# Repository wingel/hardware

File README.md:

# Miscellaneous hardware projects by Christer Weinigel

See [LICENSE.md](LICENSE.md) for licensing.

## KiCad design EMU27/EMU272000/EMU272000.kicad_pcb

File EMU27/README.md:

# En 27 series EPROM emulator

An 27-series EPROM emulator with in circuit programming.

This is the first spin and the hardware won't work properly.  /CS is
ignored so unless the EEPROM is the only device on the memory bus
reads from it can conflict with reads from other devices.

Planned EPROM variants:

| Model       | Package | Size (bits) | Size (words) | Comments		|
| ----------- | ------: | ----------: | -----------: | ----------------	|
| 27C1000     |   DIP32 |          1M |     128k x 8 |                  |
| 27C2000     |   DIP32 |          2M |     256k x 8 |                  |

# Description

A 3.3V flash memory with is used to store data.  A 5V tolerant CPLD
and a level shifter is used to do level translation between the 3.3V
flash memory and the 5V EEPROM pins.  The CPLD and level shifter can
also isolate the flash memory from the EEPROM pins so that the flash
memory can be progammed in circuit.  The 3.3V supply for the CPLD and
flash memory can be supplied from either the EEPROM pins or from the
programming connector so that the flash can be reprogrammed when the
cirucit is turned off.

The flash memory can be programmed using JTAG boundary scan using the
same JTAG connector which is also used to program the CPLD or using
(TBD - protocol to be decided) over a separate in circuit programming
connector.

PDF files with the schematics can be found in the [Docs](Docs)
directory.

# Operation

The emulator consists of two bords.  The main board (27C2000C)
contains the CPLD, flash memory and programming connectors.  Another
board contains (27C2000) the level shifter, 5V to 3.3V power supply
and EPROM pins that fit a EPROM socket.  The main reason for using two
boards are size constraints, it's hard to find a CPLD with enough pins
which can be hand soldered and which will fit between the DIP pins.
The current variant of the second board has a DIP32 footprint and
should be compatible with 27C1000 and 27C2000 EPROMs, but it should be
easy to adapt this design to to other pinouts and smaller EPROMS.

The CPLD is connected to the address (A0_5V..A17_5V) and control
(CE_5V and OE_5V) pins on the 5V EPROM side and the address (A0..A17),
data (D0..D7) and control (CE, OE and WE) on the 3.3V flash memory
side.  A level shifter also interfaces between the 5V data
(D0_5V..D7_5V) and 3.3V data (D0..D7) pins.  In normal operation the
CPLD drives the 3.3V A0..A7, CE and OE pins with the signals from the
corresponding signals on the 5V side.  The level shifter drives the 5V
D0_5V..D7_5V pins the 3.3V data pins whenever OE_5V and CE_5V are low.

TODO this is not true right now, the circuit is buggy and will drive
the D0_5V..D7_5V pins whenever OE is low; the state of CE is ignored.
This has to be fixed in a future spin of the emulator.

The reason for using a separate level shifter is mostly that I could
not find a CPLD that can be hand soldered and which would have enough
pins and fit physically on the board.  A bonus though of using a
separate level shifter is that it will actually drive 5V onto the
D0_5V..D7_5V pins which could improve compatibility if the emulator is
used in a circuit which won't work if they were driven with 3.3V.

# Tools

The [tools](tools) directory contains some quick python hacks to talk
to the emulator using JTAG boundary scan using openocd.  This
directory also contains an openocd configuration for a Raspberry Pi 3.

[emu2000_bsdl.py](tools/emu2000_bsdl.py) uses boundary scan to show
the state all pins on the emulator and toggles one of the programming
lines just to see that it can be done.

[emu2000_prog.py](tools/emu2000_prog.py) uses boundary scan to program
the first 256 bytes of the flash memory with some test data.

If you have a minipro compatible PROM programmer you can plug the
emulator into it and read out the test data with:

```bash
sudo ./minipro -p 'MX27C1000@DIP32' -r foo.bin -y
```

The "-y" flag is neccessary because the emulator is actually more of a
ROM emulator and does not present the correct chip ID:

```
Found TL866II+ 04.2.86 (0x256)
Warning: Firmware is out of date.
  Expected  04.2.128 (0x280)
    Found     04.2.86 (0x256)
    WARNING: Chip ID mismatch: expected 0xC20E, got 0xFFFF (unknown)
    Reading Code...  1.05Sec  OK
```

You will need a BSDL file for the Xilinx XC9572XL chip.  The tools
assume that Xilinx ISE is installed /opt/Xilinx and that the BSDL file
is called /opt/Xilinx/14.7/ISE_DS/ISE/xc9500xl/data/xc9572xl_vq64.bsd .

To be abls to read BSDL files this BSDL parser is used:

> https://github.com/cyrozap/python-bsdl-parser

The minipro tool can be found here:

> https://gitlab.com/DavidGriffith/minipro

# Bugs and possible improvements

CE is ignored when deciding to drive D0_5V..D7_5V, only OE is
considered.  This means that if CE is actually used as a chip select,
reads from the emulator will conflict with reads from other devices.
This can be worked around by removing R2 or U3 and driving the DIR pin
of U2 from CE (TODO have to check the polarity).  In the future,
figure out a better way of doing this.  Decode CE and OE using the
CPLD and use a free pin to drive OE of U3.  Or do it with discrete
logic (CE_5V connected to OE of U3, OE_5V connected to DIR or the
inverter).

The current spin of the emulator was intended to have an onboard
oscillator and have two two programming signals using I2C or UART.
I'm probably going to switch to using a bidirectional variant of SPI
where the SCK signal replaces the oscillator.  One less component to
mount on the PCB and this ought to simplify the logic in the FPGA
quite a bit.

Currently A18 is connected to the flash memory so that a 512kx8 flash
could be used.  That's a bit unneccesary, drive A18 low or leave it
floating instead and just don't support a larger flash than 256kx8.
This would also free up a pin on the CPLD.

It might be possible to pull CE on the flash chip to ground
permanently so that it does not have to be connected to the CPLD.
If that can be done that would free up one pin on the CPLD.

Currently A17_5V and PGM_5V are not connected to the CPLD.  Those pins
are used for the programming interface.  Relocate A17 to some other
CPLD pin so that 27C2000 emulation will work.

It would be nice if the emulation could emulate not only a ROM but
acually a PROM which responds with an ID code.  To do that we'd need
to be able to observe the PGM pin and see if it is pulled to +12V.
Not that important, but would be nice to have.

Rename the mainboard to 27EMUMAIN or maybe EMU27MAIN.

Maybe rename the other board to EMU271000.

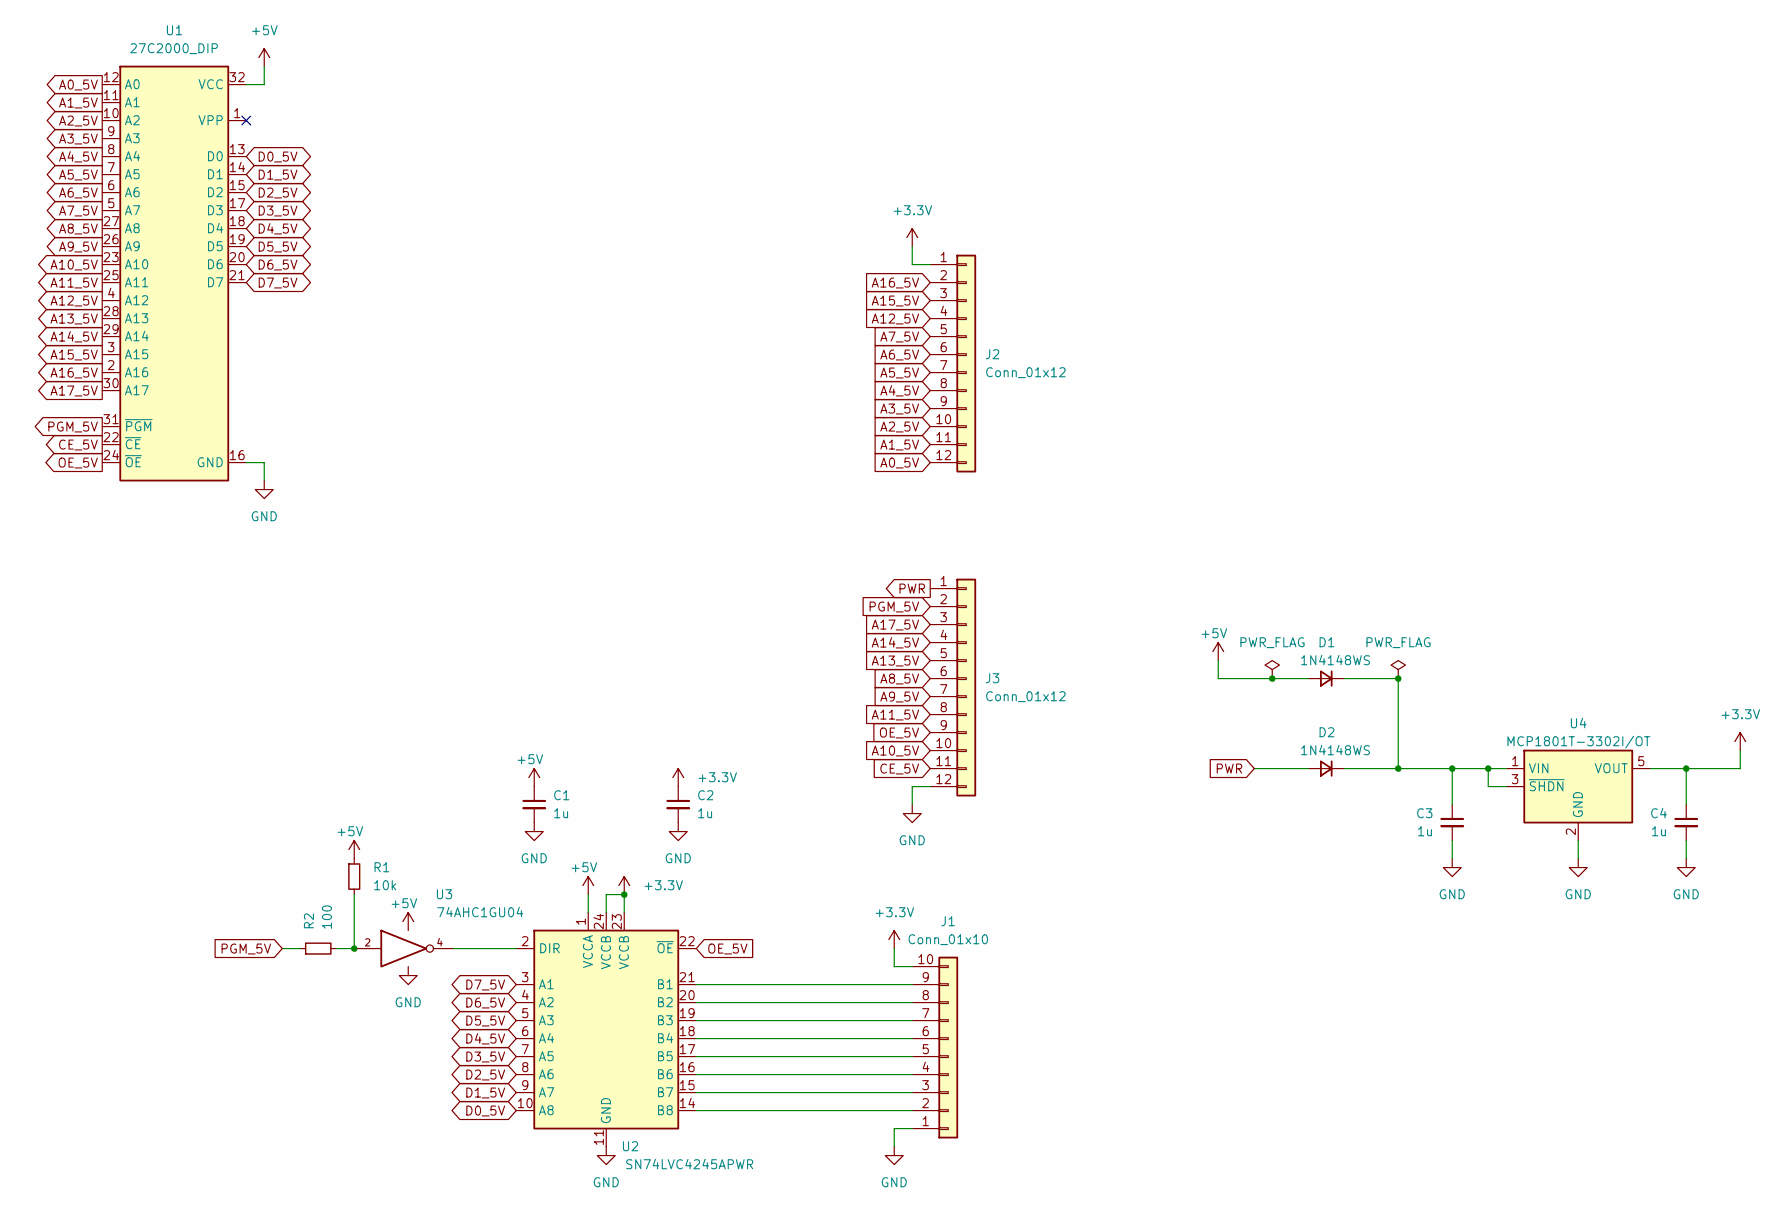
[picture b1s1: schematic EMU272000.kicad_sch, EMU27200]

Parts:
C1, C2, C3, C4: 1u; R_0603_1608Metric_Pad0.98x0.95mm_HandSolder; LCSC C52923
D1, D2: 1N4148WS; D_SOD-323F; LCSC C2128
J1: Conn_01x10; PinHeader_1x10_P1.27mm_Vertical
J2, J3: Conn_01x12; PinHeader_1x12_P1.27mm_Vertical
R1: 10k; R_0603_1608Metric_Pad0.98x0.95mm_HandSolder; LCSC C25744
R2: 100; R_0603_1608Metric_Pad0.98x0.95mm_HandSolder; LCSC C25076
U1: 27C2000_DIP; DIP-32_W15.24mm_Socket
U2: SN74LVC4245APWR; TSSOP-24_4.4x7.8mm_P0.65mm; LCSC C7859
U3: 74AHC1GU04; SOT-23-5_HandSoldering; LCSC C7465
U4: MCP1801T-3302I/OT; SOT-23-5; LCSC C84119

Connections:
+3V3: C2.1, C4.1, J1.10, J2.1, U2.23 (VCCB), U2.24 (VCCB), U4.5 (VOUT)
+5V: C1.1, D1.2 (A), R1.1, U1.32 (VCC), U2.1 (VCCA), U3.5 (VCC)
A0_5V: J2.12, U1.12 (A0)
A1_5V: J2.11, U1.11 (A1)
A2_5V: J2.10, U1.10 (A2)
A3_5V: J2.9, U1.9 (A3)
A4_5V: J2.8, U1.8 (A4)
A5_5V: J2.7, U1.7 (A5)
A6_5V: J2.6, U1.6 (A6)
A7_5V: J2.5, U1.5 (A7)
A8_5V: J3.6, U1.27 (A8)
A9_5V: J3.7, U1.26 (A9)
A10_5V: J3.10, U1.23 (A10)
A11_5V: J3.8, U1.25 (A11)
A12_5V: J2.4, U1.4 (A12)
A13_5V: J3.5, U1.28 (A13)
A14_5V: J3.4, U1.29 (A14)
A15_5V: J2.3, U1.3 (A15)
A16_5V: J2.2, U1.2 (A16)
A17_5V: J3.3, U1.30 (A17)
CE_5V: J3.11, U1.22 (~CE)
D0_5V: U1.13 (D0), U2.10 (A8)
D1_5V: U1.14 (D1), U2.9 (A7)
D2_5V: U1.15 (D2), U2.8 (A6)
D3_5V: U1.17 (D3), U2.7 (A5)
D4_5V: U1.18 (D4), U2.6 (A4)
D5_5V: U1.19 (D5), U2.5 (A3)
D6_5V: U1.20 (D6), U2.4 (A2)
D7_5V: U1.21 (D7), U2.3 (A1)
GND: C1.2, C2.2, C3.2, C4.2, J1.1, J3.12, U1.16 (GND), U2.11 (GND), U2.12 (GND), U2.13 (GND), U3.3 (GND), U4.2 (GND)
unnamed: C3.1, D1.1 (K), D2.1 (K), U4.1 (VIN), U4.3 (~SHDN)
unnamed: J1.2, U2.14 (B8)
unnamed: J1.3, U2.15 (B7)
unnamed: J1.4, U2.16 (B6)
unnamed: J1.5, U2.17 (B5)
unnamed: J1.6, U2.18 (B4)
unnamed: J1.7, U2.19 (B3)
unnamed: J1.8, U2.20 (B2)
unnamed: J1.9, U2.21 (B1)
unnamed: R1.2, R2.2, U3.2
unnamed: U2.2 (DIR), U3.4
OE_5V: J3.9, U1.24 (~OE), U2.22 (~OE)
PGM_5V: J3.2, R2.1, U1.31 (~PGM)
PWR: D2.2 (A), J3.1

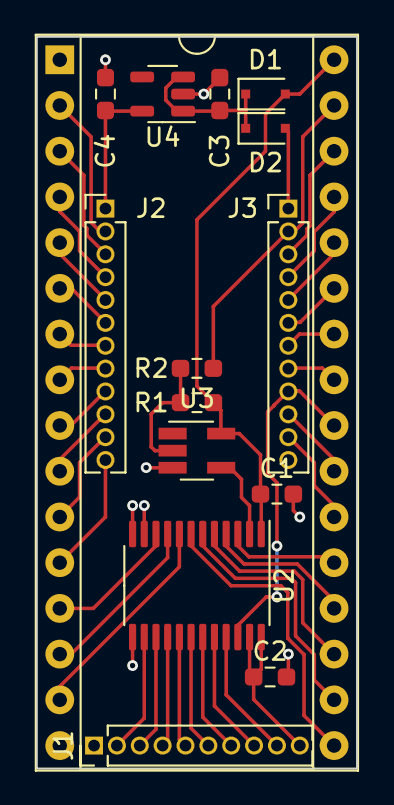
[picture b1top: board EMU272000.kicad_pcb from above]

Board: 2 copper layers, 17.8 x 40.6 mm, 15 parts (0 on the bottom side), 44 nets.

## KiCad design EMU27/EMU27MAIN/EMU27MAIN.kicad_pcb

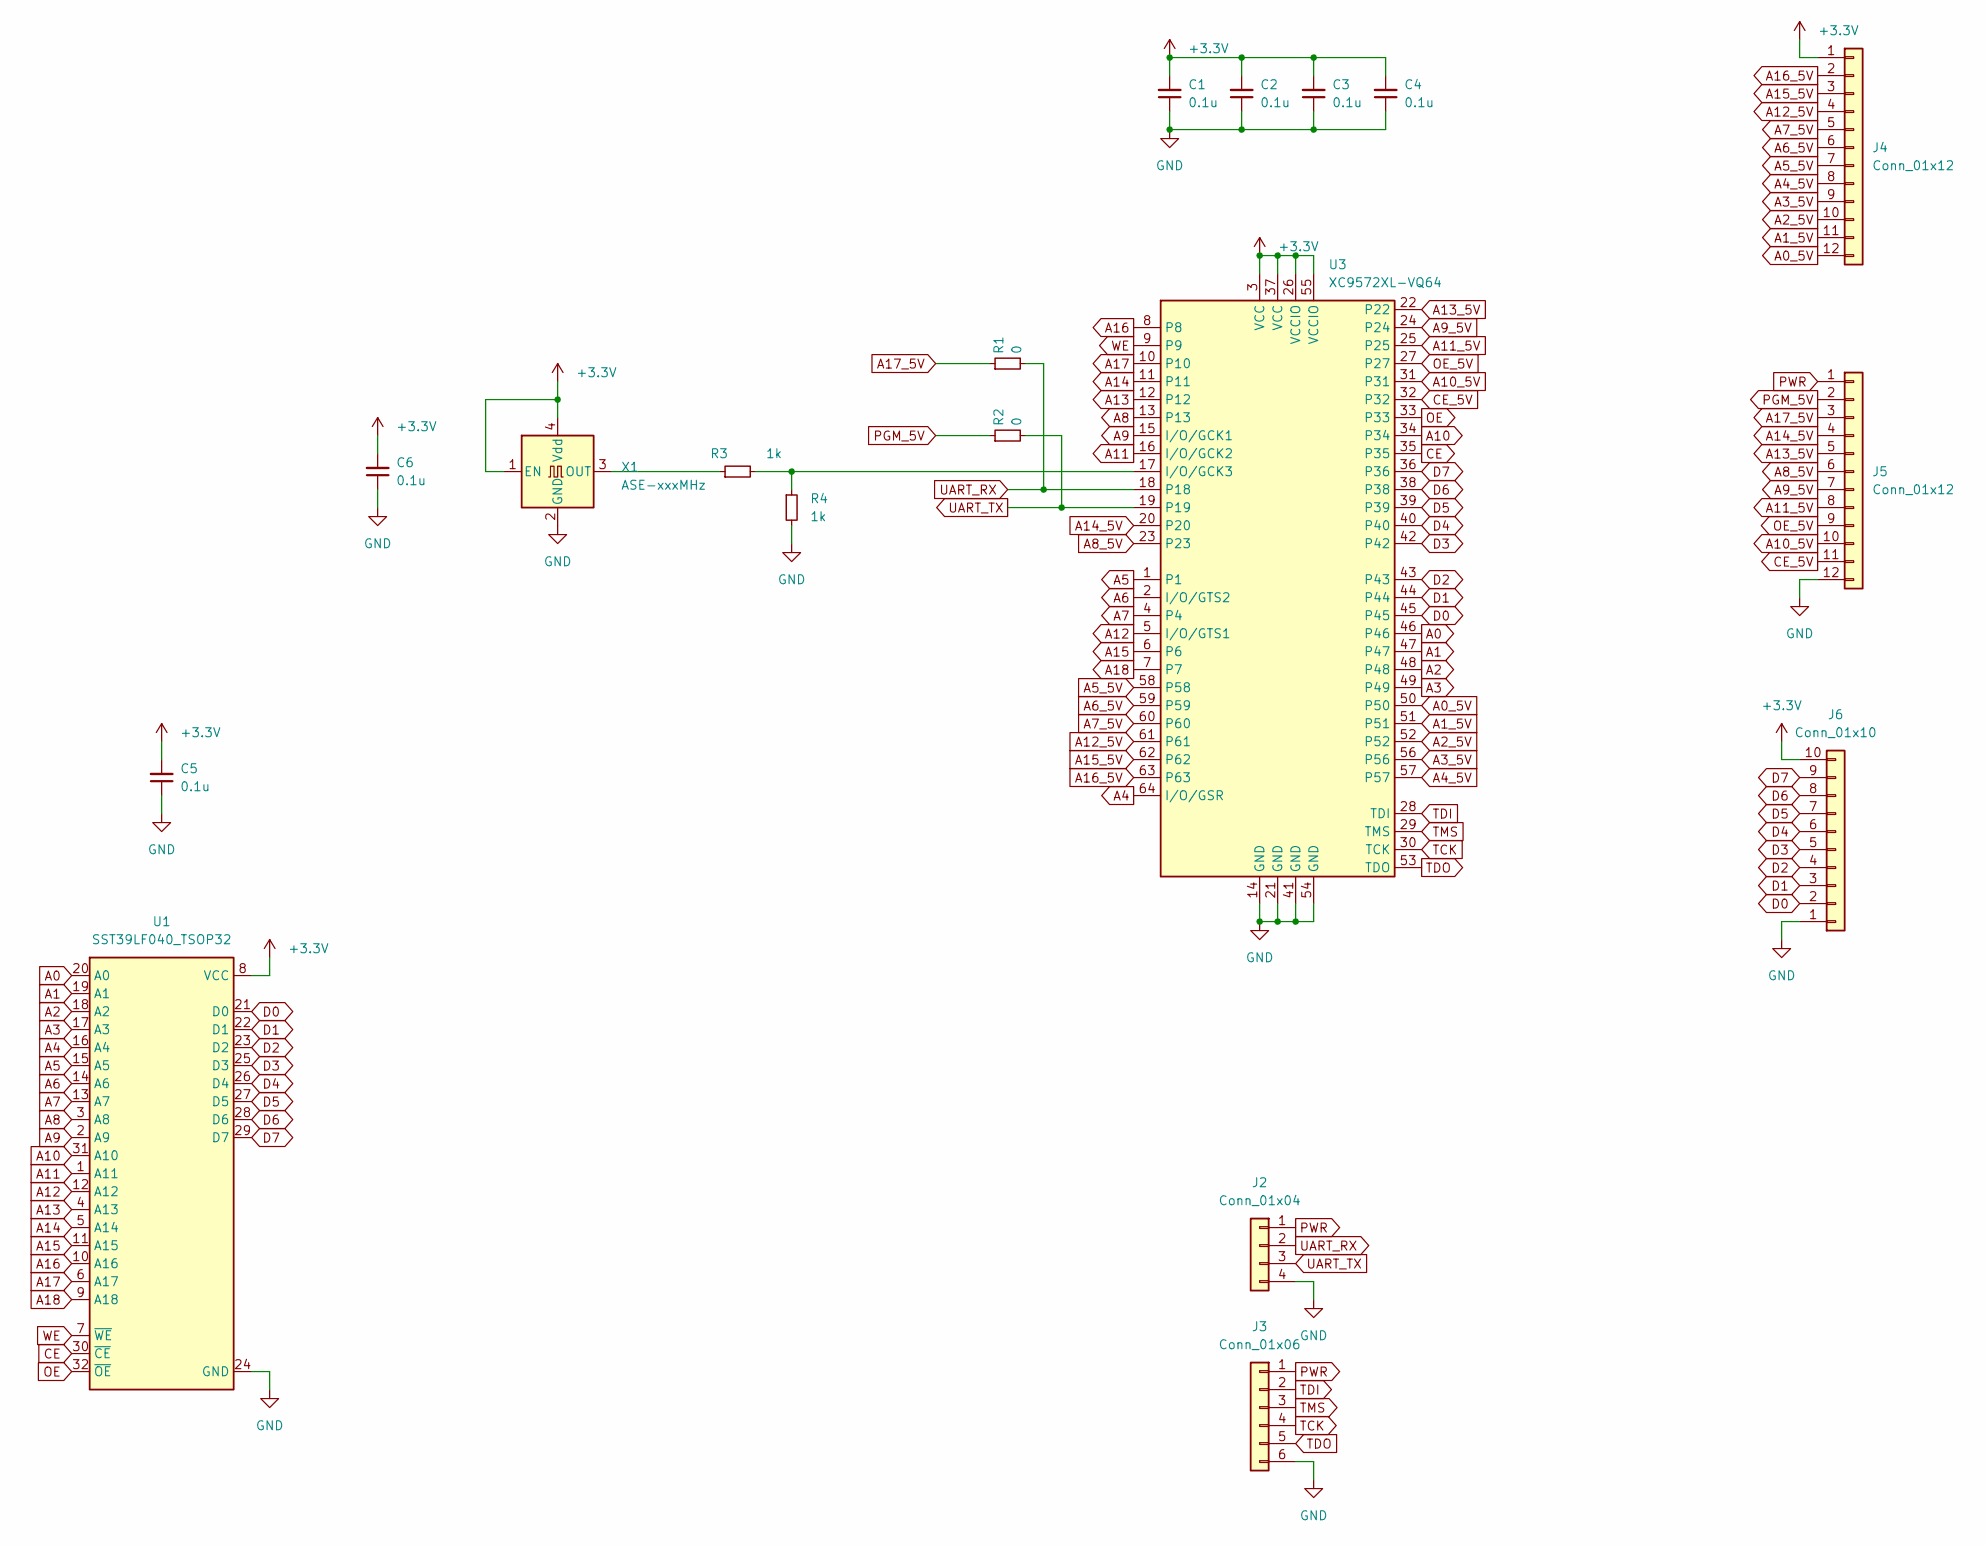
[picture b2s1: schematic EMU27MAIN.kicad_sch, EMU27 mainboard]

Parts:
C1, C2, C3, C4, C5, C6: 0.1u; R_0402_1005Metric; Voltage 16V; LCSC C1525
J2: Conn_01x04; Molex_PicoBlade_53047-0410_1x04_P1.25mm_Vertical
J3: Conn_01x06; Molex_PicoBlade_53047-0610_1x06_P1.25mm_Vertical
J4, J5: Conn_01x12; PinSocket_1x12_P1.27mm_Vertical
J6: Conn_01x10; PinSocket_1x10_P1.27mm_Vertical
R1, R2: 0; R_0402_1005Metric; LCSC C17168
R3, R4: 1k; R_0402_1005Metric
U1: SST39LF040_TSOP32; TSOP-I-32_12.4x8mm_P0.5mm
U3: XC9572XL-VQ64; TQFP-64_10x10mm_P0.5mm
X1: ASE-xxxMHz; Oscillator_SMD_Abracon_ASCO-4Pin_1.6x1.2mm

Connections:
+3V3: C1.2, C2.2, C3.2, C4.2, C5.2, C6.2, J4.1, J6.10, U1.8 (VCC), U3.3 (VCC), U3.26 (VCCIO), U3.37 (VCC), U3.55 (VCCIO), X1.1 (EN), X1.4 (Vdd)
A0: U1.20 (A0), U3.46
A0_5V: J4.12, U3.50
A1: U1.19 (A1), U3.47
A1_5V: J4.11, U3.51
A2: U1.18 (A2), U3.48
A2_5V: J4.10, U3.52
A3: U1.17 (A3), U3.49
A3_5V: J4.9, U3.56
A4: U1.16 (A4), U3.64 (I/O/GSR)
A4_5V: J4.8, U3.57
A5: U1.15 (A5), U3.1
A5_5V: J4.7, U3.58
A6: U1.14 (A6), U3.2 (I/O/GTS2)
A6_5V: J4.6, U3.59
A7: U1.13 (A7), U3.4
A7_5V: J4.5, U3.60
A8: U1.3 (A8), U3.13
A8_5V: J5.6, U3.23
A9: U1.2 (A9), U3.15 (I/O/GCK1)
A9_5V: J5.7, U3.24
A10: U1.31 (A10), U3.34
A10_5V: J5.10, U3.31
A11: U1.1 (A11), U3.16 (I/O/GCK2)
A11_5V: J5.8, U3.25
A12: U1.12 (A12), U3.5 (I/O/GTS1)
A12_5V: J4.4, U3.61
A13: U1.4 (A13), U3.12
A13_5V: J5.5, U3.22
A14: U1.5 (A14), U3.11
A14_5V: J5.4, U3.20
A15: U1.11 (A15), U3.6
A15_5V: J4.3, U3.62
A16: U1.10 (A16), U3.8
A16_5V: J4.2, U3.63
A17: U1.6 (A17), U3.10
A17_5V: J5.3, R1.1
A18: U1.9 (A18), U3.7
CE: U1.30 (~CE), U3.35
CE_5V: J5.11, U3.32
D0: J6.2, U1.21 (D0), U3.45
D1: J6.3, U1.22 (D1), U3.44
D2: J6.4, U1.23 (D2), U3.43
D3: J6.5, U1.25 (D3), U3.42
D4: J6.6, U1.26 (D4), U3.40
D5: J6.7, U1.27 (D5), U3.39
D6: J6.8, U1.28 (D6), U3.38
D7: J6.9, U1.29 (D7), U3.36
GND: C1.1, C2.1, C3.1, C4.1, C5.1, C6.1, J2.4, J3.6, J5.12, J6.1, R4.2, U1.24 (GND), U3.14 (GND), U3.21 (GND), U3.41 (GND), U3.54 (GND), X1.2 (GND)
unnamed: R3.1, X1.3 (OUT)
unnamed: R3.2, R4.1, U3.17 (I/O/GCK3)
OE: U1.32 (~OE), U3.33
OE_5V: J5.9, U3.27
PGM_5V: J5.2, R2.1
PWR: J2.1, J3.1, J5.1
TCK: J3.4, U3.30 (TCK)
TDI: J3.2, U3.28 (TDI)
TDO: J3.5, U3.53 (TDO)
TMS: J3.3, U3.29 (TMS)
UART_RX: J2.2, R1.2, U3.18
UART_TX: J2.3, R2.2, U3.19
WE: U1.7 (~WE), U3.9

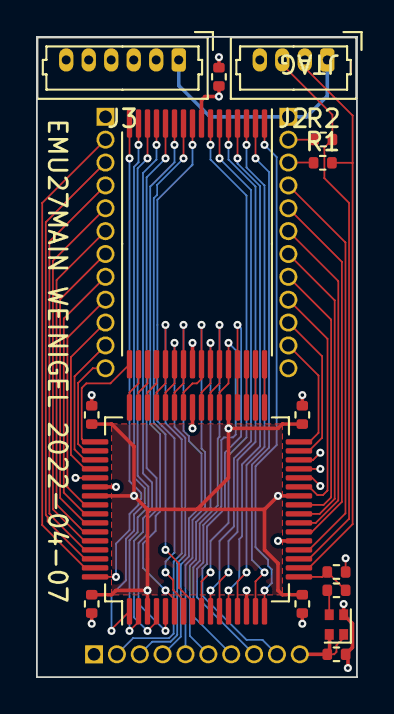
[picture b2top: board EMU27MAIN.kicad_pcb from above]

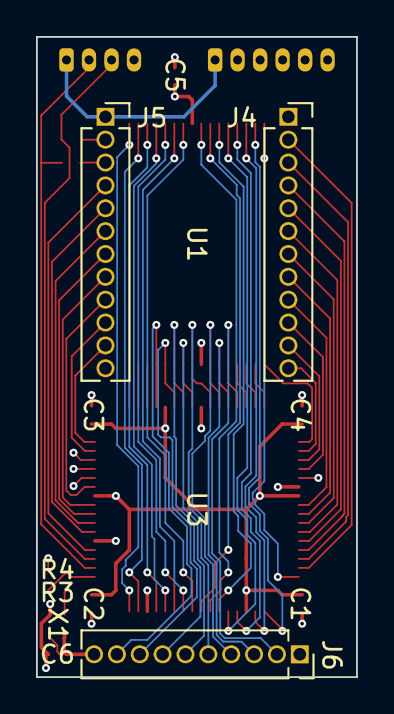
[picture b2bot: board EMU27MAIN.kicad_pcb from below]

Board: 4 copper layers, 17.8 x 35.6 mm, 18 parts (3 on the bottom side), 62 nets.

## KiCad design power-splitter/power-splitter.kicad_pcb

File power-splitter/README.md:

# A GPS power splitter with optional LNA

This is a simple three way power splitter intented to be used with a
GPS receiver and an active antenna.

The splitter has a built in bias-T which can pass DC, allowing an
active antenna to be connected to the input to be powered from a GPS
receiver connected to output port 1.

The design also also has optional space for adding a Mini-Circuits
PSA-5451+ or PSA-5453+ low noise amplifier (LNA) which is powered from
the same bias-T via a MIC5365 LDO.  The LDO allows the splitter to be
powered from 3.3V to 5V.

Just about any through hole SMA or MCX connector with 5.08mm / 0.2"
spacing between the ground pins can be used.

This design has been manufactured using a 4 layer board from JLCPCB
using their recommended trace widths to get 50 Ohm traces with the
JLC7628 stackup.  The board can also use the JLCPCB assembly service
letting them place most components on the board.

# Resistive splitter theory

A good summary of the theory can be found on
[the Microwaves101 page on resistive power splitters](https://www.microwaves101.com/encyclopedias/resistive-power-splitters).

One of the simplest N-way resistive splitters consists of a junction
with N+1 identical branches with a series resistor on each branch
which matches the impedances of each branch.  For a N way splitter the
resistor should be:

> R = Z0 * (N-1) / (N+1) Ohm

The loss from the input to each output will be:

> 10 * log10((1 / N) ** 2) dB

For a three way 50 Ohm splitter like this one the series resistance
should then be:

> 50 * (3-1) / (3+1) = 25 Ohms

The theoretical loss from the input to each output will be:

> 10*log10((1/3)**2) = -9.54 dB

As a verification that the calculated resistance is correct, look from
the junction point at the three output branches.  Assume that each
output is terminated in 50 Ohm.  Add the 25 Ohm resistors in series
giving a total of 75 Ohm on each branch.  Seen from the junction point
there will be three 75 Ohm resistors in parallel to ground giving a
total resistance of:

> 1 / (1/75 + 1/75 + 1/75) = 75/3 = 25 Ohms

Add the 25 Ohm resistor on the input branch and the total impedance
seen from the input port will be 50 Ohm.

Since 25 Ohm is not a common resistance, the schematic uses two
resistors in series (10 Ohm + 15 Ohm) from the more common E12 series
of resistors to get the correct resistance.

# Optional LNA

The design for the optional LNA in the schematic is basically the
"recommended application circuit" from the
[Mini-Circuits PSA-5351+ data sheet](https://www.minicircuits.com/pdfs/PSA-5451+.pdf).
This LNA should be usable from 50 MHz up to 4 GHz and have gain from
about 22 dB at low frequencies to 10 dB at high frequencies.  With the
resistive splitter having about a 10 dB loss the combination of LNA
and splitter should have a gain from the input to an output of about
10 dB at the low frequencies to 0 dB at the high frequencies.

To make it possible to switch between using the LNA or not, the
footprints for capacitors C1 and C3 on the input and resistors R8 and
R11 on the output overlap.  To use the design as a passive splitter,
use C3 and R11.  To use the design with the LNA, mount the LNA and LDO
and their passives and use C1 and R8.

It should also be possible to use a
[Mini-Circuits PSA-5453+ LNA](https://www.minicircuits.com/pdfs/PSA-5453+.pdf)
which has slightly higher gain.  In that case change bias resistor R6
to 681 Ohm.

# Manufacturing using JLCPCB

This design has been manufactured using JLCPCB's assembly service
letting them place most components.  The schematic contains the JLCPCB
part numers for the components that JLCPCB keep in stock.  As
configured the splitter is built for the LNA variant but withouth the
PSA-5451+ LNA itself since JLCPCB does not have it in stock.

## Create the files needed to manufacture the PCBs

Open the PCB Editor and use the "File" menu, "Fabrication Outputs" and
then both "Gerbers" and "Drill Files".

This will create a bunch of ".gbr" files with the gerber files for the
PCB and ".drl" files with the drills.

Create a zip file all the fabrication outputs.

```bash
rm -f power-splitter.zip
zip power-splitter.zip power-splitter-*.{gbr,drl}
```

Upload the file "power-splitter.zip" when ordering the PCBs.  Make
sure to use the "JLC7628" stackup and to select "Impedance" and "Yes"
to get an impedance controlled board.

## Create the files needed to assemble the PCBs

Open the Schematic Editor and export the BOM file using any of the
choices found from the "Tools" menu and "Generate BOM".  For some
reason this gives an error message but it doesn't matter since it does
create the XML file which is needed by jlc-kicad-tools below.

Open the PCB Editor and use the "File" menu, "Fabrication Outputs" and
"Component Placement".

The BOM and placement files from KiCad are not directly compatible
with JLCPCBs assembly service, but there is a nice tool called
[jlc-kicad-tools](https://github.com/matthewlai/JLCKicadTools) which
can take the KiCad files and modify them so that they will work JLCCB.

Install jlc-kicad-tools:

```bash
pip3 install jlc-kicad-tools
```

Open a shell prompt in the directory and convert the files to JLCPCB
compatible files.

```bash
jlc-kicad-tools .
```

Upload the files "power-splitter_bom_jlc.csv" and
"power-splitter_cpl_jlc.csv" when ordering the assembly service.

# TODO

The PCB layout for the LNA in this design is different from the
recommended layout.  It also uses a different inductor L3 with higher
resistance than recommended just to keep costs down.  If I ever respin
this board I probably should try to use the recommended layout and
recommended inductor instead of the ones I'm using right now.  The
current design works decently, but it might be possible to improve it.

The layout could probably be improved to reduce the impedance
mismatches for the SMA connectors.

Can the input/output matching be improved.

Redo the design to fit in some existing enclosure, maybe something
like the Hammond 1455D601.  Or if it's possible to find some RF
shielded enclosure of similar size.

Add a small shield can over the LNA and splitter components on the
PCB.

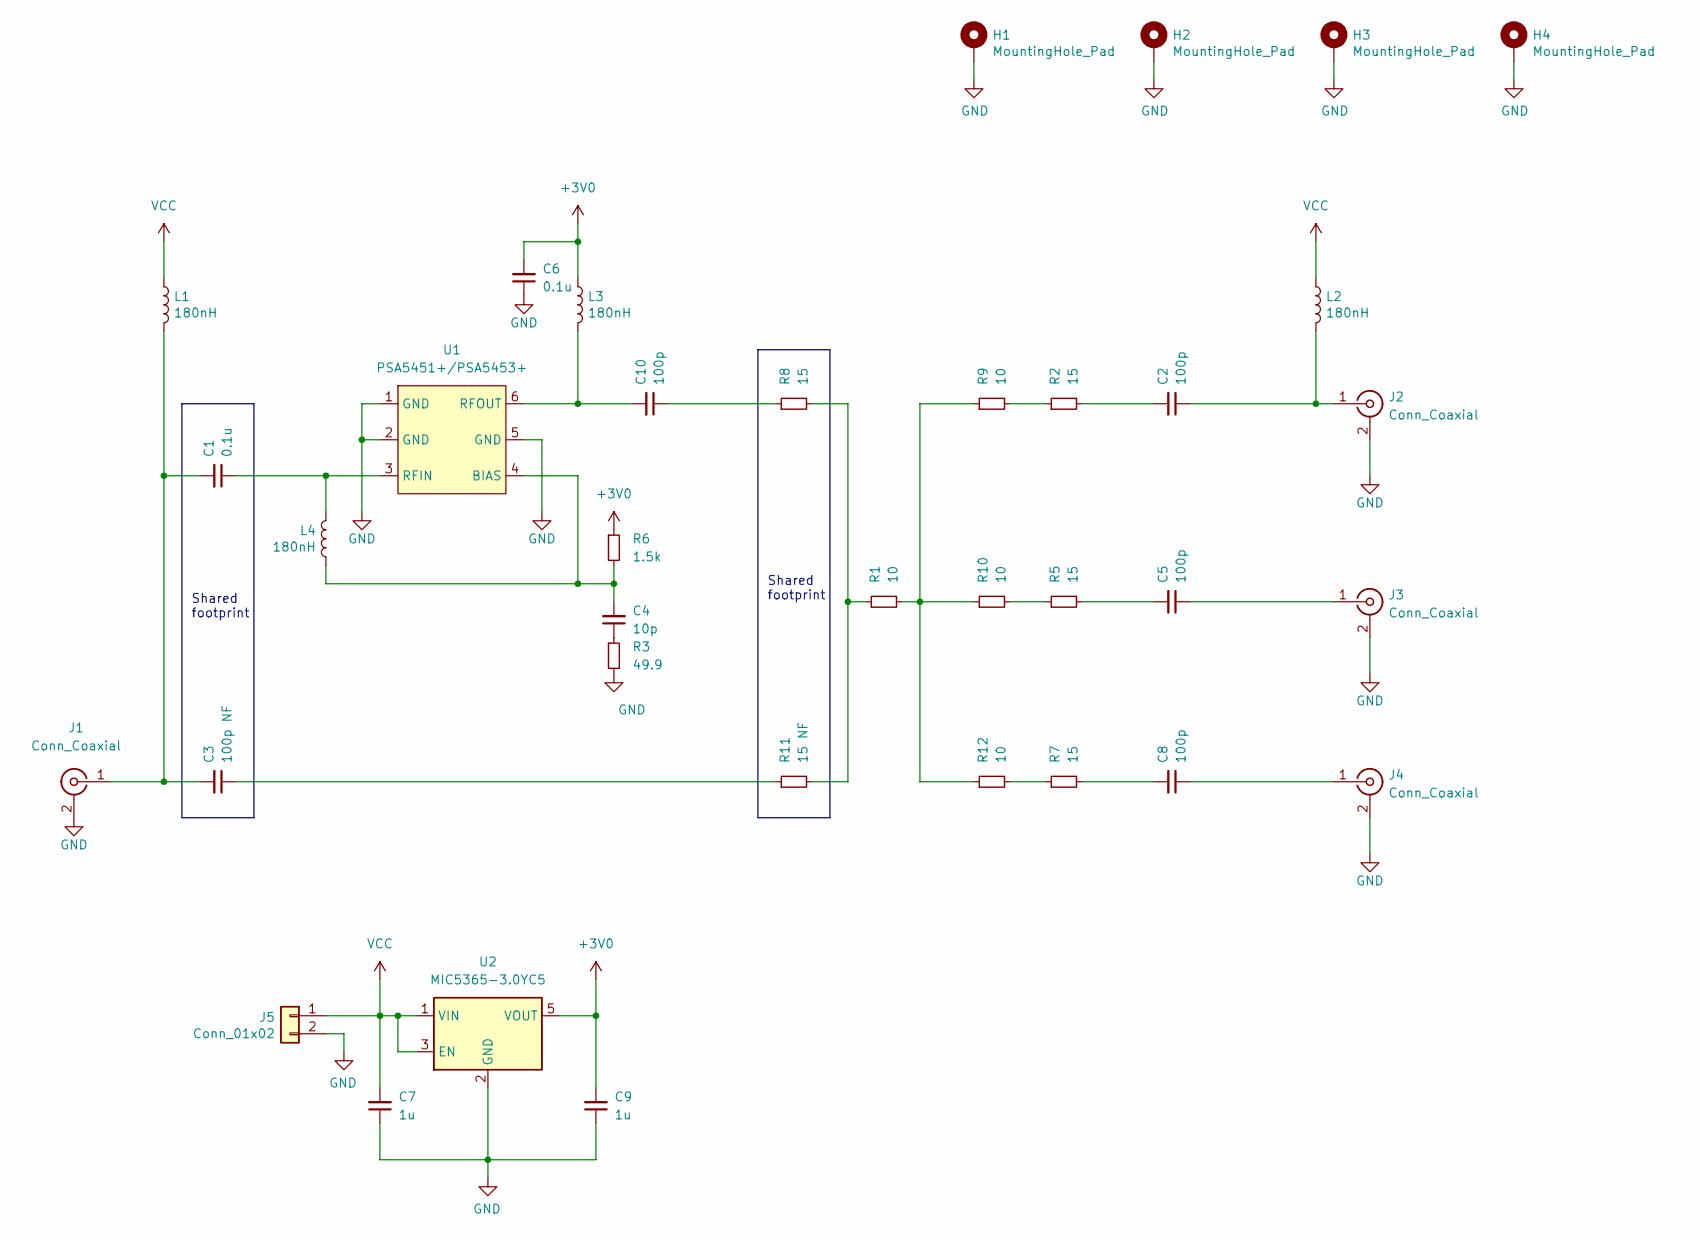
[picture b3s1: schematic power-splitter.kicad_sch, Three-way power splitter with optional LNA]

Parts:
C1, C6: 0.1u; R_0402_1005Metric; Voltage 16V; LCSC C1525
C2, C5, C8, C10: 100p; R_0402_1005Metric; Voltage 16V; LCSC C1546
C3: 100p NF; R_0402_1005Metric; Voltage 16V
C4: 10p; R_0402_1005Metric; Voltage 16V; LCSC C32949
C7, C9: 1u; R_0402_1005Metric; Voltage 16V; LCSC C52923
H1, H2, H3, H4: MountingHole_Pad; PLATED_HOLE_6MM_3.2MM
J1, J2, J3, J4: Conn_Coaxial; SMA_Amphenol_132203-12_Horizontal
J5: Conn_01x02; PinHeader_1x02_P2.54mm_Vertical
L1, L2, L3, L4: 180nH; R_0402_1005Metric; LCSC C185484
R1, R9, R10, R12: 10; R_0402_1005Metric; LCSC C25077
R2, R5, R7, R8: 15; R_0402_1005Metric; LCSC C25083
R3: 49.9; R_0402_1005Metric; LCSC C25120
R6: 1.5k; R_0402_1005Metric; LCSC C25867
R11: 15 NF; R_0402_1005Metric
U1: PSA5451+/PSA5453+; SOT-363_SC-70-6
U2: MIC5365-3.0YC5; SOT-353_SC-70-5; LCSC C220617

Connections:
+3V0: C6.2, C9.2, L3.1, R6.1, U2.5 (VOUT)
GND: C6.1, C7.1, C9.1, H1.1, H2.1, H3.1, H4.1, J1.2 (Ext), J2.2 (Ext), J3.2 (Ext), J4.2 (Ext), J5.2, R3.2, U1.1 (GND), U1.2 (GND), U1.5 (GND), U2.2 (GND)
unnamed: C1.1, L4.1, U1.3 (RFIN)
unnamed: C1.2, C3.2, J1.1 (In), L1.2
unnamed: C2.1, J2.1 (In), L2.2
unnamed: C2.2, R2.2
unnamed: C3.1, R11.1
unnamed: C4.1, R3.1
unnamed: C4.2, L4.2, R6.2, U1.4 (BIAS)
unnamed: C5.1, J3.1 (In)
unnamed: C5.2, R5.2
unnamed: C8.1, J4.1 (In)
unnamed: C8.2, R7.2
unnamed: C10.1, R8.1
unnamed: C10.2, L3.2, U1.6 (RFOUT)
unnamed: R1.1, R8.2, R11.2
unnamed: R1.2, R9.1, R10.1, R12.1
unnamed: R2.1, R9.2
unnamed: R5.1, R10.2
unnamed: R7.1, R12.2
VCC: C7.2, J5.1, L1.1, L2.1, U2.1 (VIN), U2.3 (EN)

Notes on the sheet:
Shared footprint

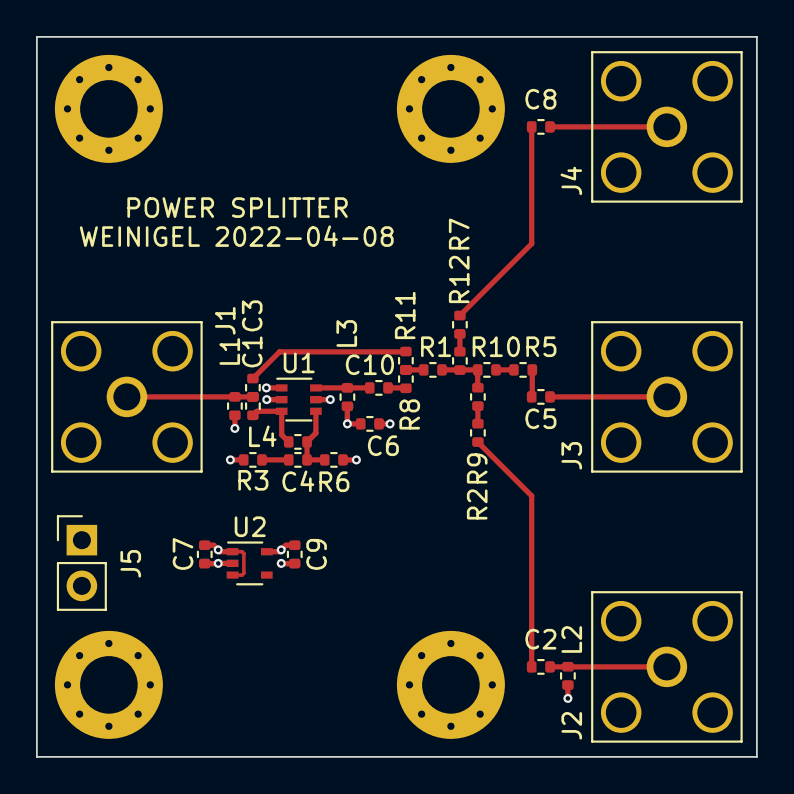
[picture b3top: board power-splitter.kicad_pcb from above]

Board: 4 copper layers, 40.0 x 40.0 mm, 36 parts (0 on the bottom side), 21 nets.

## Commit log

2022-04-24 Add README.md, LICENSE.md and .gitignore
2022-04-24 Add power-splitter KiCad project
2022-05-16 Add EMU27 project
2022-05-24 Add EMU27 spi slave test code
2022-05-24 remove dump.vcd
2022-05-24 fixes

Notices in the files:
power-splitter/power-splitter.kicad_sch:
MIT License or Creative Commons BY
